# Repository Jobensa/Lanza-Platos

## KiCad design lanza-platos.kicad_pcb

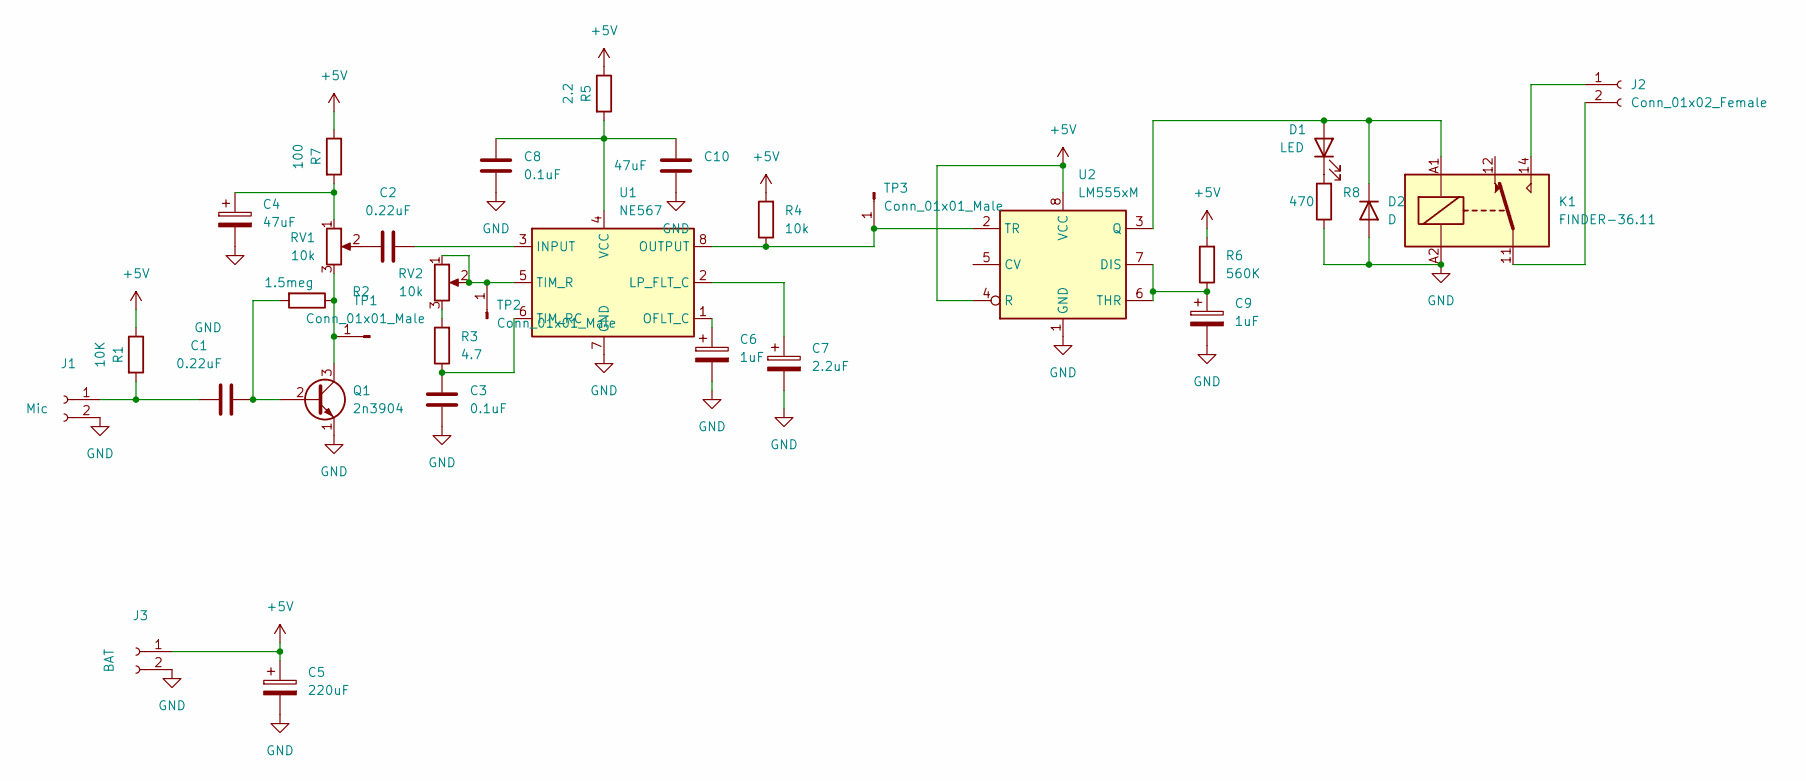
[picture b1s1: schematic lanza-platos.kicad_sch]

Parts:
C1, C2: 0.22uF; C_Disc_D4.7mm_W2.5mm_P5.00mm
C3, C8: 0.1uF; C_Disc_D4.7mm_W2.5mm_P5.00mm
C4, C10: 47uF; CP_Radial_D5.0mm_P2.50mm
C5: 220uF; CP_Radial_D7.5mm_P2.50mm
C6, C9: 1uF; CP_Radial_D5.0mm_P2.50mm
C7: 2.2uF; CP_Radial_D5.0mm_P2.50mm
D1: LED; LED_D5.0mm
D2: D; D_DO-15_P10.16mm_Horizontal
J1: Mic; PinHeader_1x02_P2.54mm_Vertical
J2: Conn_01x02_Female; PinHeader_1x02_P2.54mm_Vertical
J3: BAT; PinHeader_1x02_P2.54mm_Vertical
K1: FINDER-36.11; Relay_SPDT_Finder_36.11
Q1: 2n3904; TO-92_Inline
R1: 10K; R_Axial_DIN0207_L6.3mm_D2.5mm_P7.62mm_Horizontal
R2: 1.5meg; R_Axial_DIN0207_L6.3mm_D2.5mm_P7.62mm_Horizontal
R3: 4.7; R_Axial_DIN0207_L6.3mm_D2.5mm_P7.62mm_Horizontal
R4: 10k; R_Axial_DIN0207_L6.3mm_D2.5mm_P7.62mm_Horizontal
R5: 2.2; R_Axial_DIN0207_L6.3mm_D2.5mm_P7.62mm_Horizontal
R6: 560K; R_Axial_DIN0207_L6.3mm_D2.5mm_P7.62mm_Horizontal
R7: 100; R_Axial_DIN0207_L6.3mm_D2.5mm_P7.62mm_Horizontal
R8: 470; R_Axial_DIN0207_L6.3mm_D2.5mm_P7.62mm_Horizontal
RV1, RV2: 10k; Potentiometer_ACP_CA6-H2,5_Horizontal
TP1, TP2, TP3: Conn_01x01_Male; 1PIN-1-2mm
U1: NE567; DIP-8_W7.62mm_LongPads
U2: LM555xM; DIP-8_W7.62mm_LongPads

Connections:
+5V: C5.1, J3.1, R1.1, R4.2, R5.1, R6.2, R7.1, U2.4 (R), U2.8 (VCC)
GND: C3.1, C4.2, C5.2, C6.2, C7.2, C8.1, C9.2, C10.1, D2.2 (A), J1.2, J3.2, K1.A2, Q1.1 (E), R8.1, U1.7 (GND), U2.1 (GND)
unnamed: C1.1, Q1.2 (B), R2.2
unnamed: C1.2, J1.1, R1.2
unnamed: C2.1, RV1.2
unnamed: C2.2, U1.3 (INPUT)
unnamed: C3.2, R3.1, U1.6 (TIM_RC)
unnamed: C4.1, R7.2, RV1.1
unnamed: C6.1, U1.1 (OFLT_C)
unnamed: C7.1, U1.2 (LP_FLT_C)
unnamed: C9.1, R6.1, U2.6 (THR), U2.7 (DIS)
unnamed: C8.2, C10.2, R5.2, U1.4 (VCC)
unnamed: D1.1 (K), R8.2
unnamed: D1.2 (A), D2.1 (K), K1.A1, U2.3 (Q)
unnamed: J2.1, K1.14
unnamed: J2.2, K1.11
unnamed: Q1.3 (C), R2.1, RV1.3, TP1.1
unnamed: R3.2, RV2.3
unnamed: R4.1, TP3.1, U1.8 (OUTPUT), U2.2 (TR)
unnamed: RV2.1, RV2.2, TP2.1, U1.5 (TIM_R)

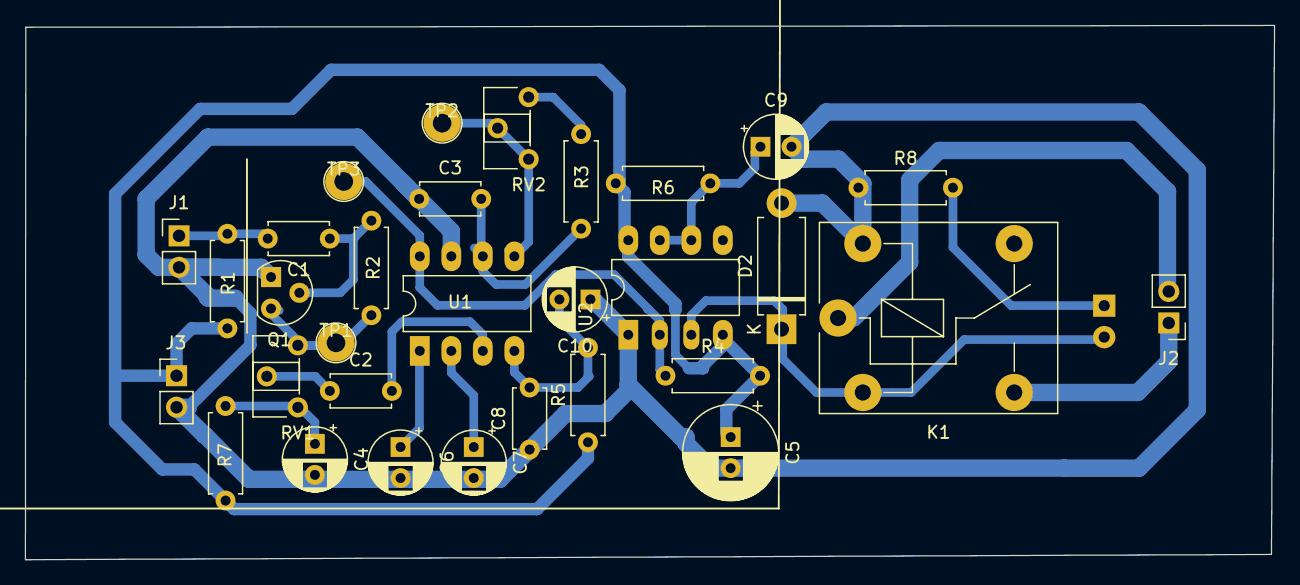
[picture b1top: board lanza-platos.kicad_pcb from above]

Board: 2 copper layers, 100.7 x 43.0 mm, 32 parts (1 on the bottom side), 20 nets.

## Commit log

2024-06-28 Version funcional 2
